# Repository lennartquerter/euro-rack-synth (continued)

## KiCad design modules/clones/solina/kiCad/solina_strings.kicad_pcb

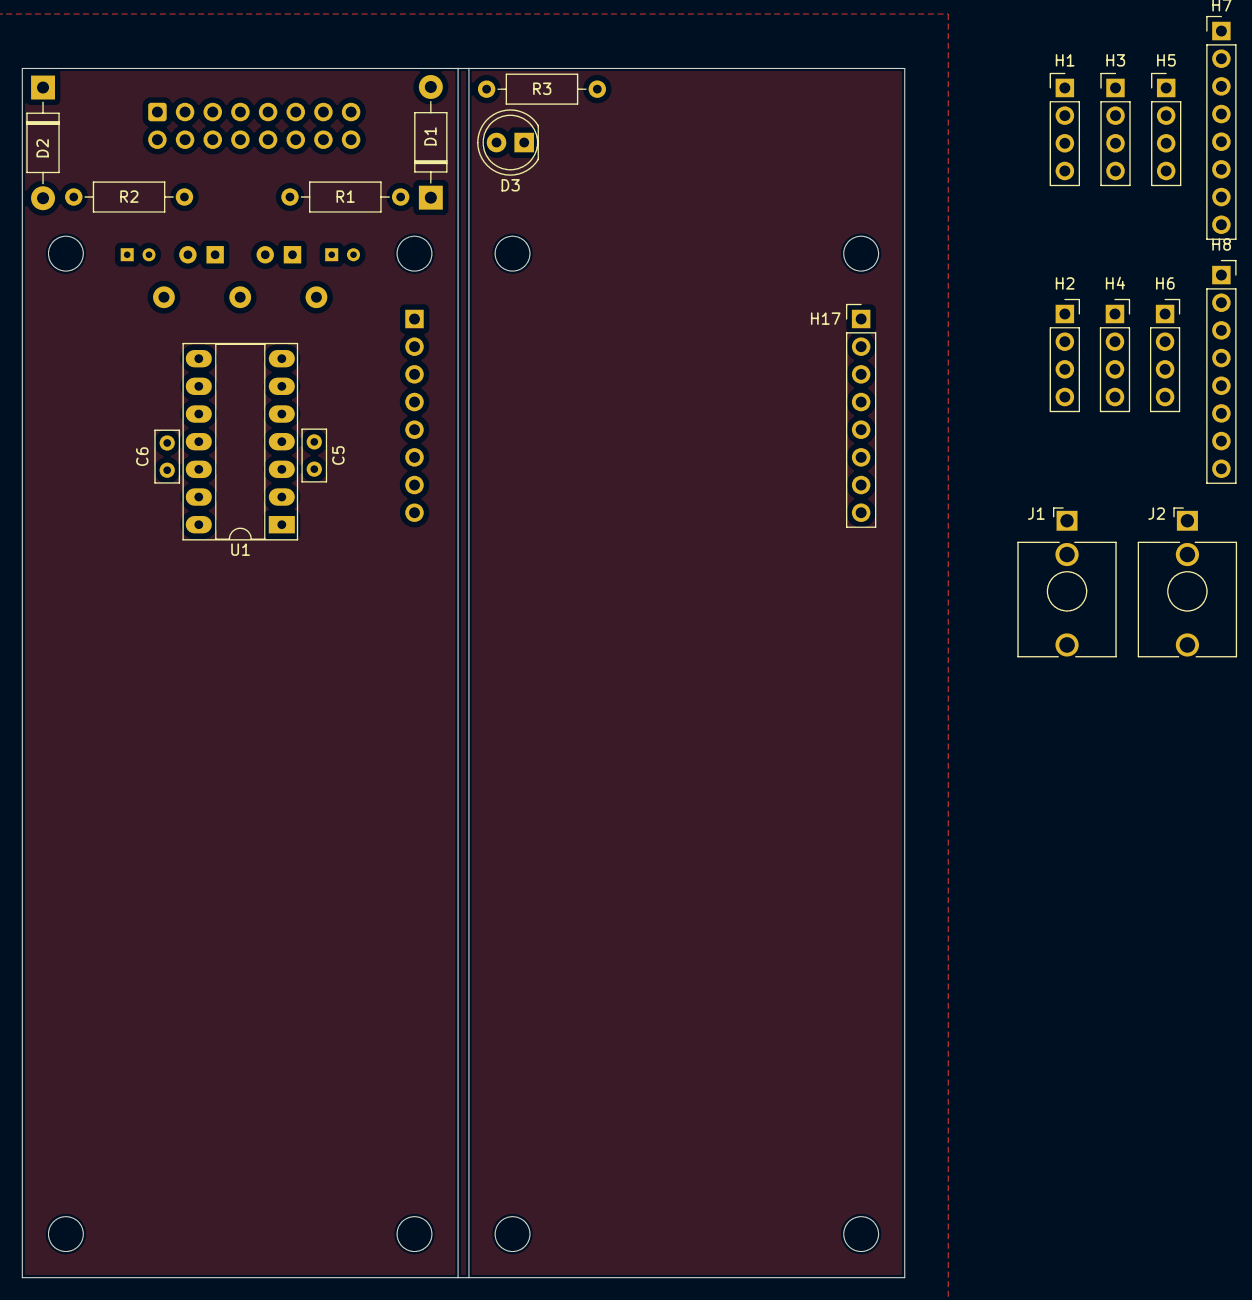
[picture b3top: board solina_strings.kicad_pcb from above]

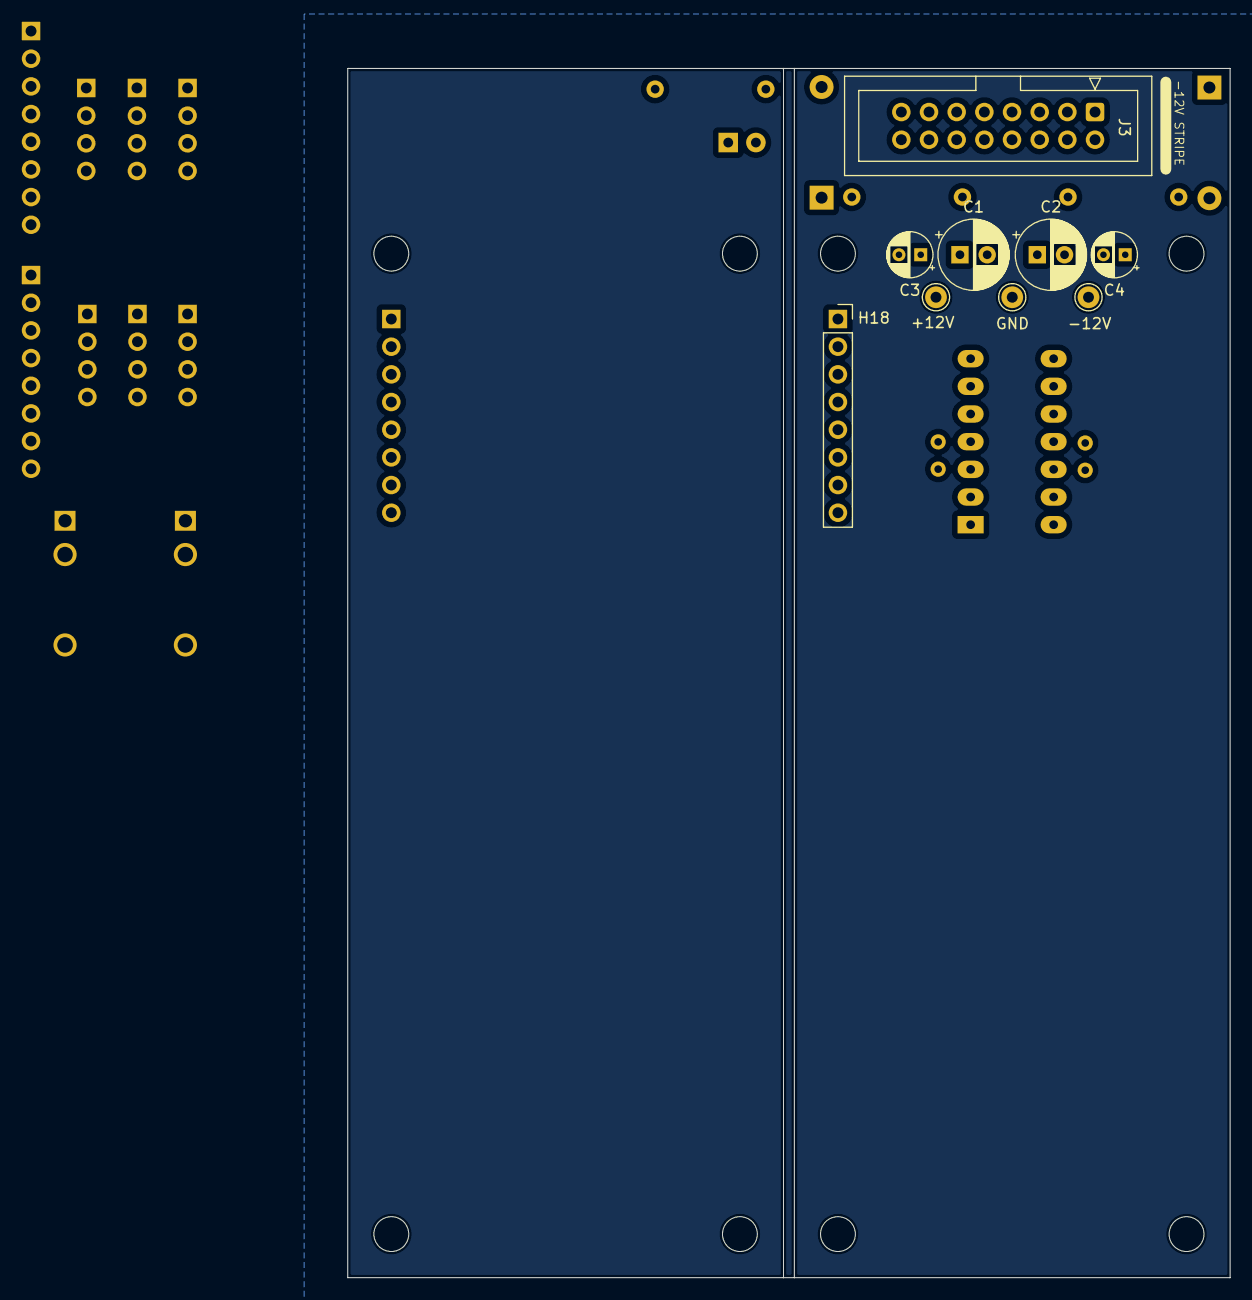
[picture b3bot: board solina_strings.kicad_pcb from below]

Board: 2 copper layers, 81.0 x 111.0 mm, 37 parts (9 on the bottom side), 12 nets, no tracks yet.

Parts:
C1, C2: 47uF; CP_Radial_D6.3mm_P2.50mm
C3, C4: 0.1uF; CP_Radial_D4.0mm_P2.00mm
C5, C6: 0.1uF; C_Rect_L4.6mm_W2.0mm_P2.50mm_MKS02_FKP02
D1, D2: 1N5819; D_DO-41_SOD81_P10.16mm_Horizontal
D3: LED; LED_D5.0mm (center Aligned)
H1: H1; PinHeader_1x04_P2.54mm_Vertical
H2: H3; PinSocket_1x04_P2.54mm_Vertical
H3: H5; PinHeader_1x04_P2.54mm_Vertical
H4: H6; PinSocket_1x04_P2.54mm_Vertical
H5: H7; PinHeader_1x04_P2.54mm_Vertical
H6: H8; PinSocket_1x04_P2.54mm_Vertical
H7: H2; PinHeader_1x08_P2.54mm_Vertical
H8: H4; PinSocket_1x08_P2.54mm_Vertical
H9, H10, H11, H12, H13, H14, H15, H16: MountingHole; MountingHole_3.2mm_M3
H17: H17; PinHeader_1x08_P2.54mm_Vertical
H18: H18; PinSocket_1x08_P2.54mm_Vertical
J1: INPUT; Jack_3.5mm_QingPu_WQP-PJ398SM_Vertical_CircularHoles
J2: OUTPUT; Jack_3.5mm_QingPu_WQP-PJ398SM_Vertical_CircularHoles
J3: PWR; IDC-Header_2x08_P2.54mm_Vertical
R1, R2: 10; R_Default (DIN0207)
R3: 500R; R_Default (DIN0207)
TP1: +12V; Pin_D1.0mm_L10.0mm
TP2: GND; Pin_D1.0mm_L10.0mm
TP3: -12V; Pin_D1.0mm_L10.0mm
U1: TL074; DIP-14_W7.62mm_Socket_LongPads

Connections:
+12V: C1.1, C3.1, C5.1, D3.2 (A), H17.1, H17.2, H18.1 (Pin_3), H18.2, R1.2, TP1.1, U1.4 (V+)
-12V: C2.2, C4.2, C6.2, H17.7, H17.8, H18.7, H18.8, R2.2, TP3.1, U1.11 (V-)
GNDREF: C1.2, C2.1, C3.2, C4.1, C5.2, C6.1, H17.3, H17.4, H17.5, H17.6, H18.3, H18.4, H18.5, H18.6, J1.S, J2.S, J3.3 (GND), J3.4 (GND), J3.5 (GND), J3.6 (GND), J3.7 (GND), J3.8 (GND), R3.1, TP2.1, U1.3 (+), U1.5 (+), U1.10 (+), U1.12 (+)
unnamed: D1.2 (A), J3.9 (+12V), J3.10 (+12V)
unnamed: D1.1 (K), R1.1
unnamed: D2.2 (A), R2.1
unnamed: D2.1 (K), J3.1 (-12V), J3.2 (-12V)
unnamed: D3.1 (K), R3.2
unnamed: U1.1, U1.2 (-)
unnamed: U1.6 (-), U1.7
unnamed: U1.8, U1.9 (-)
unnamed: U1.13 (-), U1.14

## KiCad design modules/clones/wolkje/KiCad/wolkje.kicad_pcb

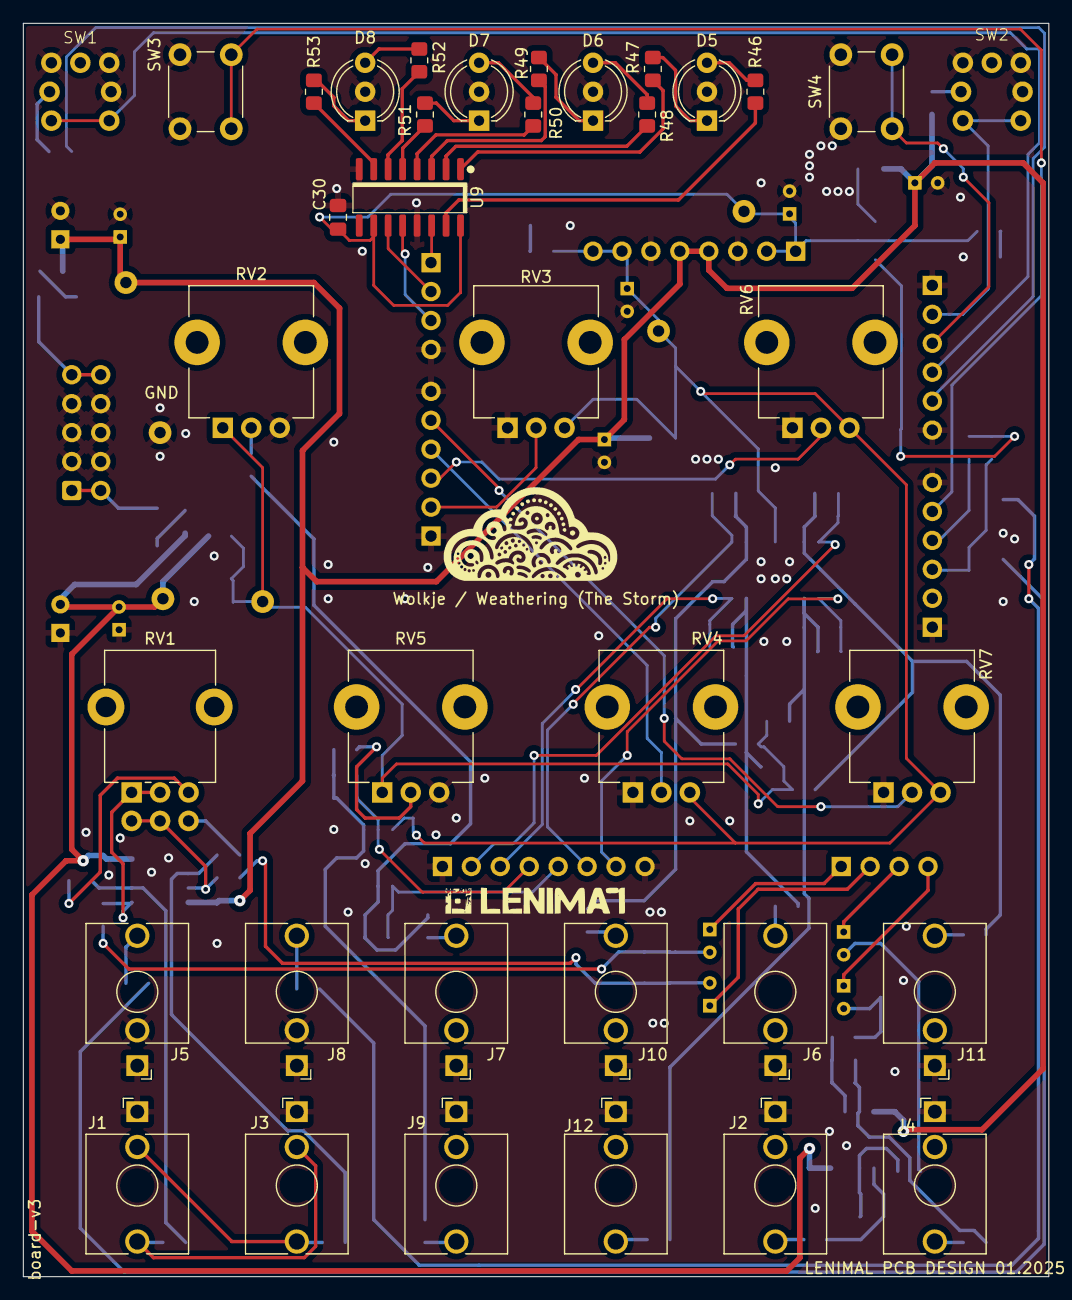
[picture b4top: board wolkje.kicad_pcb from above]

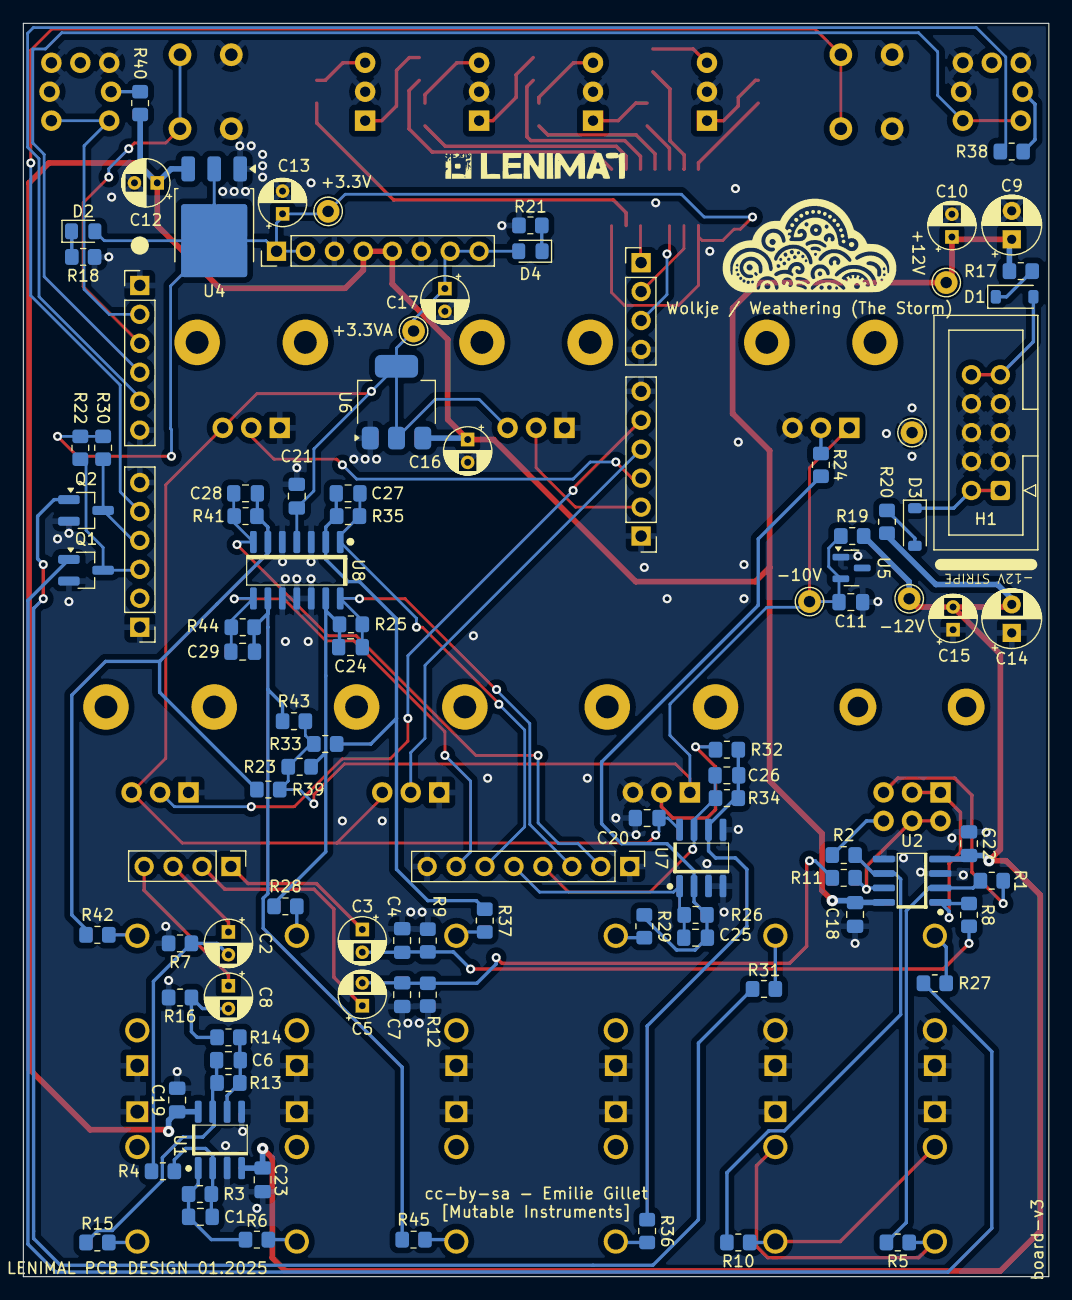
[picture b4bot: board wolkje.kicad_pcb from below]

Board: 2 copper layers, 90.0 x 110.0 mm, 132 parts (95 on the bottom side), 90 nets.

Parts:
C1, C6: 18pF; C_0805_2012Metric_Pad1.18x1.45mm_HandSolder
C2, C3, C5, C8, C12, C13, C16, C17: 10uF; CP_Radial_D4.0mm_P2.00mm
C4, C7: 220pF; C_0805_2012Metric_Pad1.18x1.45mm_HandSolder
C9, C14: 47uF; CP_Radial_D5.0mm_P2.50mm
C10, C15: 100nF; CP_Radial_D4.0mm_P2.00mm
C11, C18, C19, C20, C21, C22, C23, C30: 100nF; C_0805_2012Metric_Pad1.18x1.45mm_HandSolder
C24, C25, C26, C27, C28, C29: 1nF; C_0805_2012Metric_Pad1.18x1.45mm_HandSolder
D1, D3: 1N5819; D_SOD-123
D2, D4: LED; LED_0805_2012Metric_Pad1.15x1.40mm_HandSolder
D5: LED_4; LED_D5.0mm-3_DUAL
D6: LED_3; LED_D5.0mm-3_DUAL
D7: LED_2; LED_D5.0mm-3_DUAL
D8: LED_1; LED_D5.0mm-3_DUAL
H1: Conn_02x05_PWR_Eurorack; IDC-Header_2x05_P2.54mm_Vertical
J1: IN_L; Jack_3.5mm_QingPu_WQP-PJ398SM_Vertical_CircularHoles
J2: OUT_L; Jack_3.5mm_QingPu_WQP-PJ398SM_Vertical_CircularHoles
J3: IN_R; Jack_3.5mm_QingPu_WQP-PJ398SM_Vertical_CircularHoles
J4: OUT_R; Jack_3.5mm_QingPu_WQP-PJ398SM_Vertical_CircularHoles
J5: FREEZE_IN; Jack_3.5mm_QingPu_WQP-PJ398SM_Vertical_CircularHoles
J6: V/OCT_IN; Jack_3.5mm_QingPu_WQP-PJ398SM_Vertical_CircularHoles
J7: POSITION_IN; Jack_3.5mm_QingPu_WQP-PJ398SM_Vertical_CircularHoles
J8: TRIGGER_IN; Jack_3.5mm_QingPu_WQP-PJ398SM_Vertical_CircularHoles
J9: DENSITY_IN; Jack_3.5mm_QingPu_WQP-PJ398SM_Vertical_CircularHoles
J10: SIZE_IN; Jack_3.5mm_QingPu_WQP-PJ398SM_Vertical_CircularHoles
J11: BLEND_IN; Jack_3.5mm_QingPu_WQP-PJ398SM_Vertical_CircularHoles
J12: TEXTURE_IN; Jack_3.5mm_QingPu_WQP-PJ398SM_Vertical_CircularHoles
Q1, Q2: MMBT3904; SOT-23_Handsoldering
R1, R2: 3K3; R_0805_2012Metric_Pad1.20x1.40mm_HandSolder
R3, R7, R13, R16: 39K; R_0805_2012Metric_Pad1.20x1.40mm_HandSolder
R4, R8, R9, R11, R12, R14: 5K6; R_0805_2012Metric_Pad1.20x1.40mm_HandSolder
R5, R10: 22K; R_0805_2012Metric_Pad1.20x1.40mm_HandSolder
R6, R15: 1K; R_0805_2012Metric_Pad1.20x1.40mm_HandSolder
R17, R20: 10R; R_0805_2012Metric_Pad1.20x1.40mm_HandSolder
R18, R21, R38, R40: 2K; R_0805_2012Metric_Pad1.20x1.40mm_HandSolder
R19: 470R; R_0805_2012Metric_Pad1.20x1.40mm_HandSolder
R22, R30: 10K; R_0805_2012Metric_Pad1.20x1.40mm_HandSolder
R23: 180K; R_0805_2012Metric_Pad1.20x1.40mm_HandSolder
R24, R32, R33, R39, R43: 200K; R_0805_2012Metric_Pad1.20x1.40mm_HandSolder
R25: 47K; R_0805_2012Metric_Pad1.20x1.40mm_HandSolder
R26, R34, R44: 66.5K; R_0805_2012Metric_Pad1.20x1.40mm_HandSolder
R27, R28, R29, R31, R36, R37, R42, R45: 100K; R_0805_2012Metric_Pad1.20x1.40mm_HandSolder
R35, R41: 33K; R_0805_2012Metric_Pad1.20x1.40mm_HandSolder
R46, R47, R48, R49, R50, R51, R52, R53: 680R; R_0805_2012Metric_Pad1.20x1.40mm_HandSolder
RV1: A50K; Potentiometer_Alpha_RD902F
RV2, RV3, RV4, RV5, RV6, RV7: B10K; Potentiometer_TT_P0915N
SW1, SW2: SW_ML6; ML6-H2T2GQA
SW3: SW_RESEVERD; SW_PUSH_6mm
SW4: SW_MODE; SW_PUSH_6mm
TP1: GND; Pin_D1.0mm_L10.0mm
TP2: +3.3V; Pin_D1.0mm_L10.0mm
TP3: -10V; Pin_D1.0mm_L10.0mm
TP4: +12V; Pin_D1.0mm_L10.0mm
TP5: -12V; Pin_D1.0mm_L10.0mm
TP6: +3.3VA; Pin_D1.0mm_L10.0mm
U1, U2: TL072; SOIC-8
U3: wolkje-brain
U4: LM1117-3.3; TO-252-3_TabPin2
U5: LM4040DBZ-10; SOT-23
U6: LM1117-3.3; SOT-223-3_TabPin2
U7: MCP6002; SOIC-8
U8: MCP6004; SOIC-14
U9: 74HC595; SOIC-16

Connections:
+3.3V: C13.1, C30.2, D2.2 (A), R22.2, R30.2, TP2.1, U3.41 (+3.3V), U3.42 (+3.3V), U4.2 (VO), U9.10 (~SRCLR), U9.16 (VCC)
+3.3VA: C17.1, C20.1, C21.1, D4.2 (A), RV3.3, RV4.3, RV6.3, RV7.3, TP6.1, U3.35 (+3.3VA), U3.36 (+3.3VA), U6.2 (VO), U7.8 (V+), U8.4 (V+)
+12V: C9.1, C10.1, C12.1, C16.1, C18.1, C19.1, R17.2, R40.2, TP4.1, U1.8 (V+), U2.8 (V+), U3.38 (+12V), U3.39 (+12V), U4.3 (VI), U6.3 (VI)
-10V: C11.2, R19.2, R23.1, R33.1, R39.1, R43.1, RV2.1, RV5.1, TP3.1, U5.2 (A)
-12V: C14.2, C15.2, C22.2, C23.2, R19.1, R20.2, TP5.1, U1.4 (V-), U2.4 (V-)
/inputs/BLEND: RV7.2, U3.29 (Blend)
/inputs/BLEND_CV: C28.1, R41.2, U3.23 (CV_Blend), U8.7
/inputs/DENSITY: C26.1, R34.2, U3.21 (CV_Density), U7.7
/inputs/FREEZE_LED: R38.2, U3.5 (LED_FREEZE)
/inputs/FREEZE_TRIGGER: Q1.3 (C), R22.1, U3.10 (TRIG_Freeze)
/inputs/PITCH: RV6.2, U3.27 (Pitch)
/inputs/PLAY_TRIGGER: Q2.3 (C), R30.1, U3.9 (TRIG_Play)
/inputs/POSITION: C25.1, R26.2, U3.20 (CV_Position), U7.1
/inputs/SIZE: RV3.2, U3.26 (Size)
/inputs/SIZE_CV: C27.1, R35.2, U3.19 (CV_Size), U8.1
/inputs/SW_FREEZE: SW1.1, SW1.2, U3.4 (SW_Freeze)
/inputs/SW_LOAD: SW2.1, SW2.2, U3.2 (SW_Load)
/inputs/SW_MODE: SW4.2, U3.3 (SW_Mode)
/inputs/SW_RESERVED: SW3.2, U3.8 (NC_2)
/inputs/TEXTURE: RV4.2, U3.28 (Texture)
/inputs/TEXTURE_CV: C29.1, R44.2, U3.18 (CV_Texture), U8.8
/inputs/V/OCT: C24.1, R25.2, U3.22 (CV_V/OCT), U8.14
/led_driver/CLK: U3.33 (LED_CLK), U9.11 (SRCLK)
/led_driver/ENABLE: U3.32 (LED_CS), U9.12 (RCLK)
/led_driver/SER: U3.34 (LED_DATA), U9.14 (SER)
GNDREF: C4.1, C7.1, C9.2, C10.2, C11.1, C12.2, C13.2, C14.1, C15.1, C16.2, C17.2, C18.2, C19.2, C20.2, C21.2, C22.1, C23.1, C30.1, D5.3 (K), D6.3 (K), D7.3 (K), D8.3 (K), H1.3, H1.4, H1.5, H1.6, H1.7, H1.8, J1.S, J2.S, J3.S, J4.S, J5.S, J5.TN, J6.S, J7.S, J8.S, J8.TN, J9.S, J10.S, J11.S, J12.S, Q1.2 (E), Q2.2 (E), R7.2, R9.1, R12.1, R16.2, R18.1, R21.1, RV2.3, RV3.1, RV4.1, RV5.3, RV6.1, RV7.1, SW1.3, SW1.4 (A), SW1.L2, SW2.3, SW2.4 (A), SW2.L2, SW3.1, SW4.1, TP1.1, U1.3 (+), U1.5 (+), U2.3 (+), U2.5 (+), U3.1 (VSS), U3.6 (VSS), U3.7 (VSS), U3.12 (VSS), U3.17 (VSS), U3.24 (VSS), U3.25 (VSS), U3.30 (VSS), U3.31 (VSS), U3.37 (VSS), U3.40 (VSS), U4.1 (GND), U5.1 (K), U6.1 (GND), U7.3 (+), U7.4 (V-), U7.5 (+), U8.3 (+), U8.5 (+), U8.10 (+), U8.11 (V-), U8.12 (+), U9.8 (GND), U9.13 (~OE)
unnamed: C1.1, R3.2, R6.1, U1.1
unnamed: C2.2, R4.2, R7.1
unnamed: C3.2, C4.2, R8.2, R9.2
unnamed: C5.2, C7.2, R11.2, R12.2
unnamed: C6.1, R13.2, R15.1, U1.7
unnamed: C8.2, R14.2, R16.1
unnamed: D1.2 (A), H1.9, H1.10
unnamed: D1.1 (K), R17.1
unnamed: D2.1 (K), R18.2
unnamed: D3.2 (A), R20.1
unnamed: D3.1 (K), H1.1, H1.2
unnamed: D4.1 (K), R21.2
unnamed: D5.1 (A1), R47.2
unnamed: D5.2 (A2), R46.2
unnamed: D6.1 (A1), R49.2
unnamed: D6.2 (A2), R48.2
unnamed: D7.1 (A1), R51.2
unnamed: D7.2 (A2), R50.2
unnamed: D8.1 (A1), R53.2
unnamed: D8.2 (A2), R52.2
unnamed: J1.T, J3.TN, R5.1
unnamed: J1.TN, J3.T, R10.1
unnamed: J2.T, R6.2
unnamed: J4.T, R15.2
unnamed: J5.T, R27.2
unnamed: J6.T, R28.1
unnamed: J7.T, R29.1
unnamed: J8.T, R31.2
unnamed: J9.T, R36.1
unnamed: J10.T, R37.1
unnamed: J11.T, R42.1
unnamed: J12.T, R45.1
unnamed: Q1.1 (B), R27.1
unnamed: Q2.1 (B), R31.1
unnamed: R1.2, RV1.3
unnamed: R2.2, RV1.6
unnamed: R8.1, RV1.1, RV1.2, U2.1
unnamed: R11.1, RV1.4, RV1.5, U2.7
unnamed: R24.1, RV2.2
unnamed: R32.1, RV5.2
unnamed: R38.1, SW1.L1
unnamed: R40.1, SW2.L1
unnamed: C1.2, R3.1, R4.1, U1.2 (-)
unnamed: C6.2, R13.1, R14.1, U1.6 (-)
unnamed: R1.1, R5.2, U2.2 (-)
unnamed: R2.1, R10.2, U2.6 (-)
unnamed: C3.1, U3.16 (IN_L)
unnamed: C5.1, U3.15 (IN_R)
unnamed: C2.1, U3.14 (OUT_L)
unnamed: C8.1, U3.13 (OUT_R)
unnamed: C25.2, R24.2, R26.1, R29.2, U7.2 (-)
unnamed: C26.2, R32.2, R34.1, R36.2, U7.6 (-)
unnamed: C27.2, R33.2, R35.1, R37.2, U8.2 (-)
unnamed: C28.2, R39.2, R41.1, R42.2, U8.6 (-)
unnamed: C29.2, R43.2, R44.1, R45.2, U8.9 (-)
unnamed: C24.2, R23.2, R25.1, R28.2, U8.13 (-)
unnamed: R46.1, U9.15 (QA)
unnamed: R47.1, U9.1 (QB)
unnamed: R48.1, U9.2 (QC)
unnamed: R49.1, U9.3 (QD)
unnamed: R50.1, U9.4 (QE)
unnamed: R51.1, U9.5 (QF)
unnamed: R52.1, U9.6 (QG)
unnamed: R53.1, U9.7 (QH)

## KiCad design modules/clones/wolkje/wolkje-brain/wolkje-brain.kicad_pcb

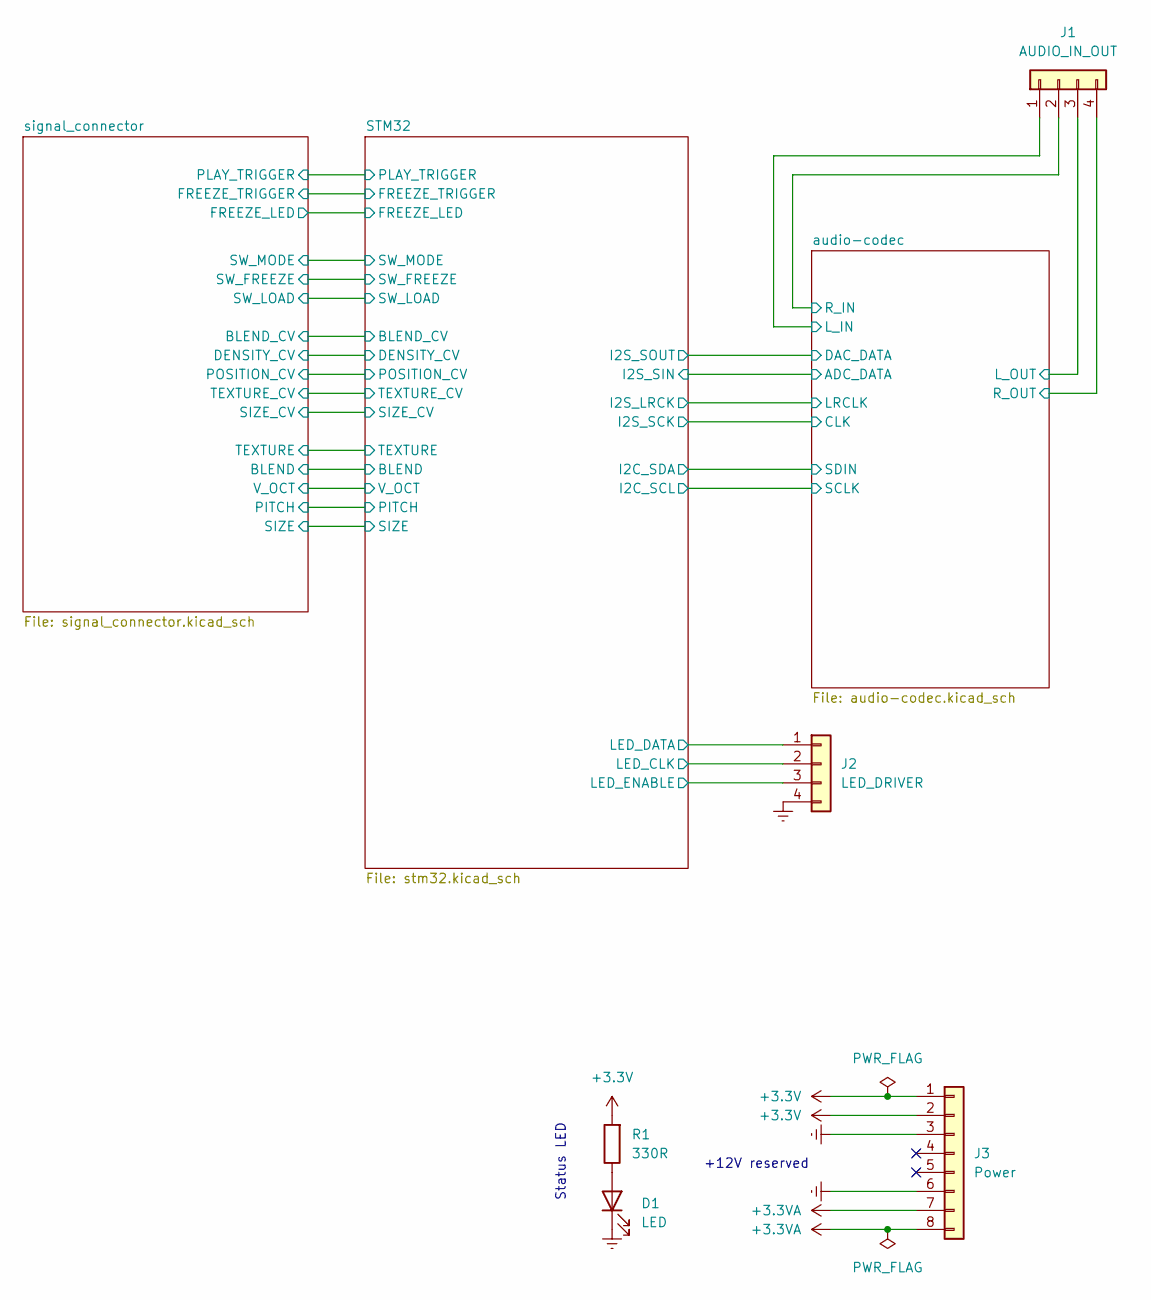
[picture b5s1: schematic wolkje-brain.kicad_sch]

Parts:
D1: LED; LED_0805_2012Metric_Pad1.15x1.40mm_HandSolder
J1: AUDIO_IN_OUT; PinHeader_1x04_P2.54mm_Vertical
J2: LED_DRIVER; PinHeader_1x04_P2.54mm_Vertical
J3: Power; PinHeader_1x08_P2.54mm_Vertical
R1: 330R; R_0805_2012Metric_Pad1.20x1.40mm_HandSolder

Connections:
+3.3V: J3.1, J3.2, R1.2; also elsewhere on the board
+3.3VA: J3.7, J3.8; also elsewhere on the board
/STM32/LED_CLK: J2.2; also elsewhere on the board
/STM32/LED_DATA: J2.1; also elsewhere on the board
/STM32/LED_ENABLE: J2.3; also elsewhere on the board
/audio-codec/L_IN: J1.1; also elsewhere on the board
/audio-codec/L_OUT: J1.3; also elsewhere on the board
/audio-codec/R_IN: J1.2; also elsewhere on the board
/audio-codec/R_OUT: J1.4; also elsewhere on the board
GNDREF: D1.1 (K), J2.4, J3.3, J3.6; also elsewhere on the board
unnamed: D1.2 (A), R1.1

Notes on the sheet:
Status LED
+12V reserved

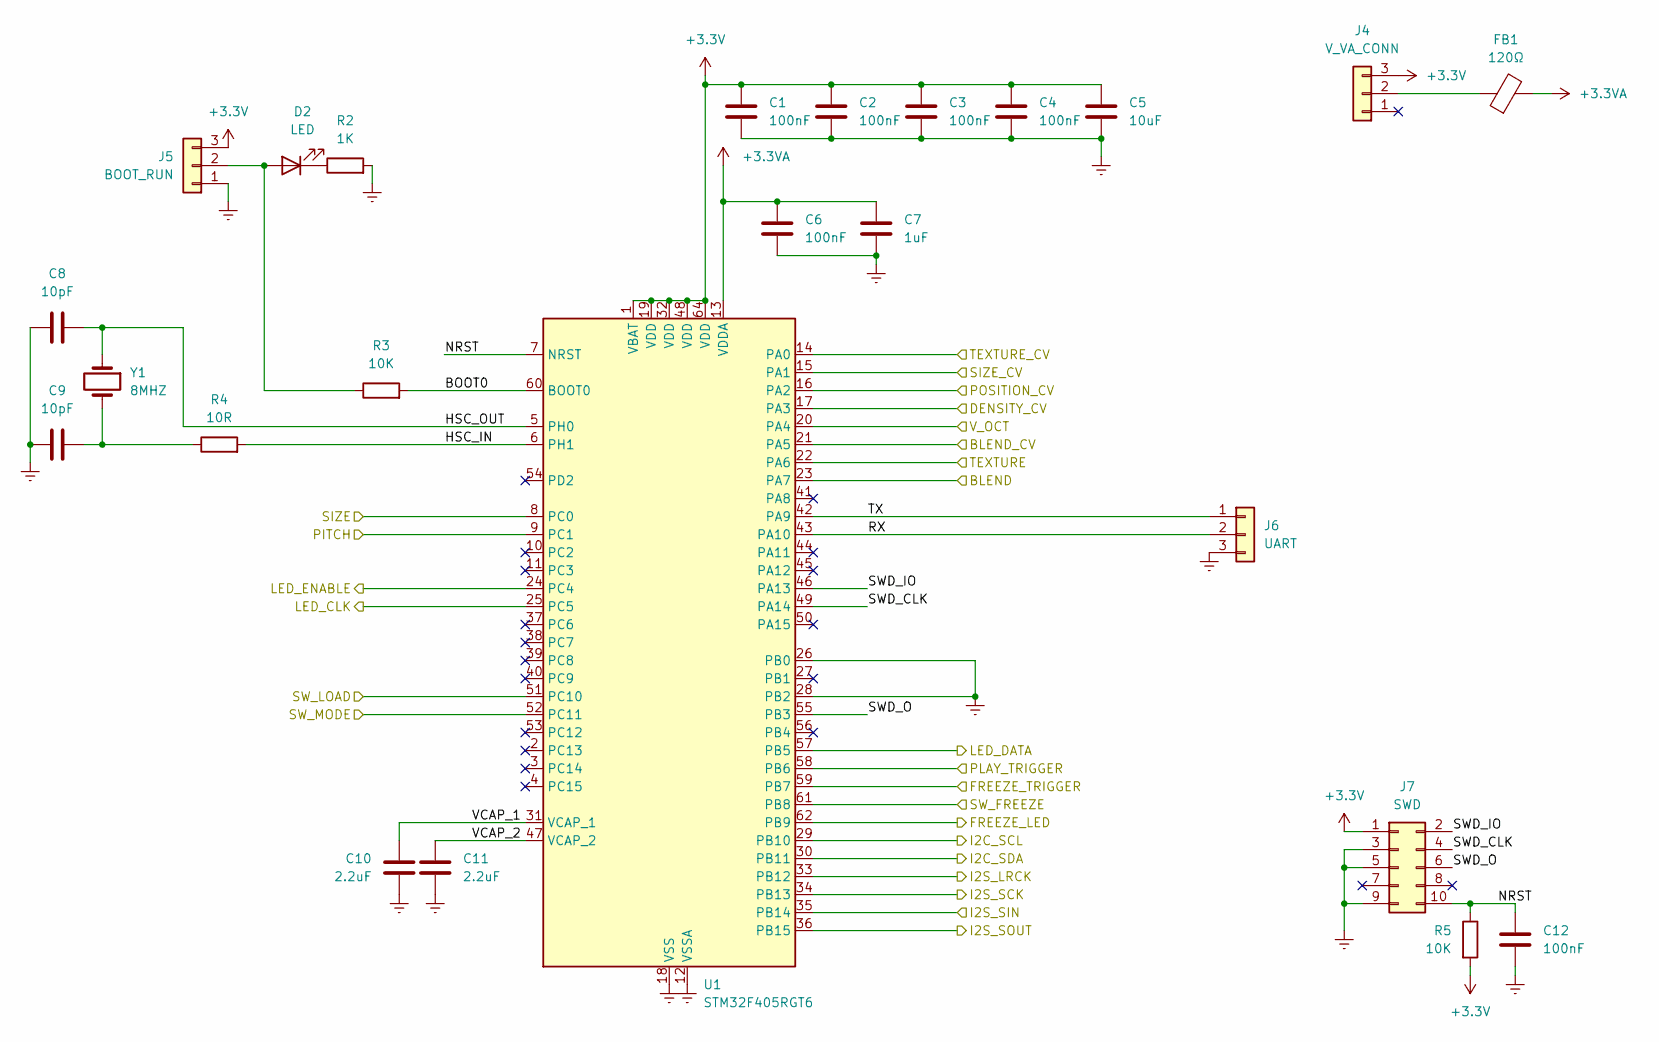
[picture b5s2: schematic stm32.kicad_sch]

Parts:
C1, C2, C3, C4, C6, C12: 100nF; C_0805_2012Metric_Pad1.18x1.45mm_HandSolder
C5: 10uF; C_0805_2012Metric_Pad1.18x1.45mm_HandSolder
C7: 1uF; C_0805_2012Metric_Pad1.18x1.45mm_HandSolder
C8, C9: 10pF; C_0805_2012Metric_Pad1.18x1.45mm_HandSolder
C10, C11: 2.2uF; C_0805_2012Metric_Pad1.18x1.45mm_HandSolder
D2: LED; LED_0805_2012Metric_Pad1.15x1.40mm_HandSolder
FB1: 120Ω; L_0805_2012Metric_Pad1.15x1.40mm_HandSolder
J4: V_VA_CONN; PinHeader_1x03_P2.54mm_Vertical
J5: BOOT_RUN; PinHeader_1x03_P2.54mm_Vertical
J6: UART; PinHeader_1x03_P2.54mm_Vertical
J7: SWD; PinHeader_2x05_P2.54mm_Vertical
R2: 1K; R_0805_2012Metric_Pad1.20x1.40mm_HandSolder
R3, R5: 10K; R_0805_2012Metric_Pad1.20x1.40mm_HandSolder
R4: 10R; R_0805_2012Metric_Pad1.20x1.40mm_HandSolder
U1: STM32F405RGT6; LQFP-64_10x10mm_P0.5mm
Y1: 8MHZ; Crystal_HC49-U_Vertical

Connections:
+3.3V: C1.2, C2.2, C3.2, C4.2, C5.2, J4.3, J5.3, J7.1, R5.2, U1.1 (VBAT), U1.19 (VDD), U1.32 (VDD), U1.48 (VDD), U1.64 (VDD); also elsewhere on the board
+3.3VA: C6.2, C7.2, FB1.2, U1.13 (VDDA); also elsewhere on the board
/STM32/BLEND: U1.23 (PA7); also elsewhere on the board
/STM32/BLEND_CV: U1.21 (PA5); also elsewhere on the board
/STM32/BOOT0: R3.2, U1.60 (BOOT0)
/STM32/DENSITY_CV: U1.17 (PA3); also elsewhere on the board
/STM32/FREEZE_LED: U1.62 (PB9); also elsewhere on the board
/STM32/FREEZE_TRIGGER: U1.59 (PB7); also elsewhere on the board
/STM32/HSC_IN: R4.2, U1.6 (PH1)
/STM32/HSC_OUT: C8.1, U1.5 (PH0), Y1.1
/STM32/I2C_SCL: U1.29 (PB10); also elsewhere on the board
/STM32/I2C_SDA: U1.30 (PB11); also elsewhere on the board
/STM32/I2S_LRCK: U1.33 (PB12); also elsewhere on the board
/STM32/I2S_SCK: U1.34 (PB13); also elsewhere on the board
/STM32/I2S_SIN: U1.35 (PB14); also elsewhere on the board
/STM32/I2S_SOUT: U1.36 (PB15); also elsewhere on the board
/STM32/LED_CLK: U1.25 (PC5); also elsewhere on the board
/STM32/LED_DATA: U1.57 (PB5); also elsewhere on the board
/STM32/LED_ENABLE: U1.24 (PC4); also elsewhere on the board
/STM32/NRST: C12.2, J7.10, R5.1, U1.7 (NRST)
/STM32/PITCH: U1.9 (PC1); also elsewhere on the board
/STM32/PLAY_TRIGGER: U1.58 (PB6); also elsewhere on the board
/STM32/POSITION_CV: U1.16 (PA2); also elsewhere on the board
/STM32/RX: J6.2, U1.43 (PA10)
/STM32/SIZE: U1.8 (PC0); also elsewhere on the board
/STM32/SIZE_CV: U1.15 (PA1); also elsewhere on the board
/STM32/SWD_CLK: J7.4, U1.49 (PA14)
/STM32/SWD_IO: J7.2, U1.46 (PA13)
/STM32/SWD_O: J7.6, U1.55 (PB3)
/STM32/SW_FREEZE: U1.61 (PB8); also elsewhere on the board
/STM32/SW_LOAD: U1.51 (PC10); also elsewhere on the board
/STM32/SW_MODE: U1.52 (PC11); also elsewhere on the board
/STM32/TEXTURE: U1.22 (PA6); also elsewhere on the board
/STM32/TEXTURE_CV: U1.14 (PA0); also elsewhere on the board
/STM32/TX: J6.1, U1.42 (PA9)
/STM32/VCAP_1: C10.1, U1.31 (VCAP_1)
/STM32/VCAP_2: C11.1, U1.47 (VCAP_2)
/STM32/V_OCT: U1.20 (PA4); also elsewhere on the board
GNDREF: C1.1, C2.1, C3.1, C4.1, C5.1, C6.1, C7.1, C8.2, C9.2, C10.2, C11.2, C12.1, J5.1, J6.3, J7.3, J7.5, J7.9, R2.2, U1.12 (VSSA), U1.18 (VSS), U1.26 (PB0), U1.28 (PB2), U1.63 (VSS); also elsewhere on the board
unnamed: C9.1, R4.1, Y1.2
unnamed: D2.2 (A), J5.2, R3.1
unnamed: D2.1 (K), R2.1
unnamed: FB1.1, J4.2

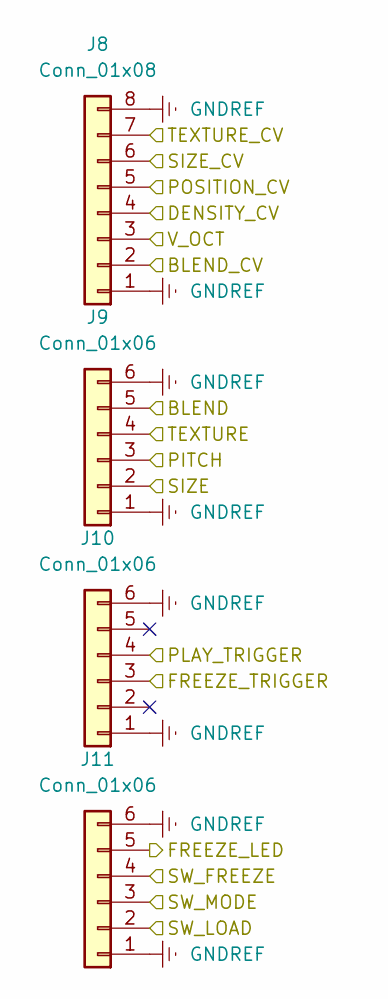
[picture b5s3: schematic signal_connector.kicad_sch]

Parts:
J8: Conn_01x08; PinHeader_1x08_P2.54mm_Vertical
J9, J10, J11: Conn_01x06; PinHeader_1x06_P2.54mm_Vertical

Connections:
/STM32/BLEND: J9.5; also elsewhere on the board
/STM32/BLEND_CV: J8.2; also elsewhere on the board
/STM32/DENSITY_CV: J8.4; also elsewhere on the board
/STM32/FREEZE_LED: J11.5; also elsewhere on the board
/STM32/FREEZE_TRIGGER: J10.3; also elsewhere on the board
/STM32/PITCH: J9.3; also elsewhere on the board
/STM32/PLAY_TRIGGER: J10.4; also elsewhere on the board
/STM32/POSITION_CV: J8.5; also elsewhere on the board
/STM32/SIZE: J9.2; also elsewhere on the board
/STM32/SIZE_CV: J8.6; also elsewhere on the board
/STM32/SW_FREEZE: J11.4; also elsewhere on the board
/STM32/SW_LOAD: J11.2; also elsewhere on the board
/STM32/SW_MODE: J11.3; also elsewhere on the board
/STM32/TEXTURE: J9.4; also elsewhere on the board
/STM32/TEXTURE_CV: J8.7; also elsewhere on the board
/STM32/V_OCT: J8.3; also elsewhere on the board
GNDREF: J8.1, J8.8, J9.1, J9.6, J10.1, J10.6, J11.1, J11.6; also elsewhere on the board

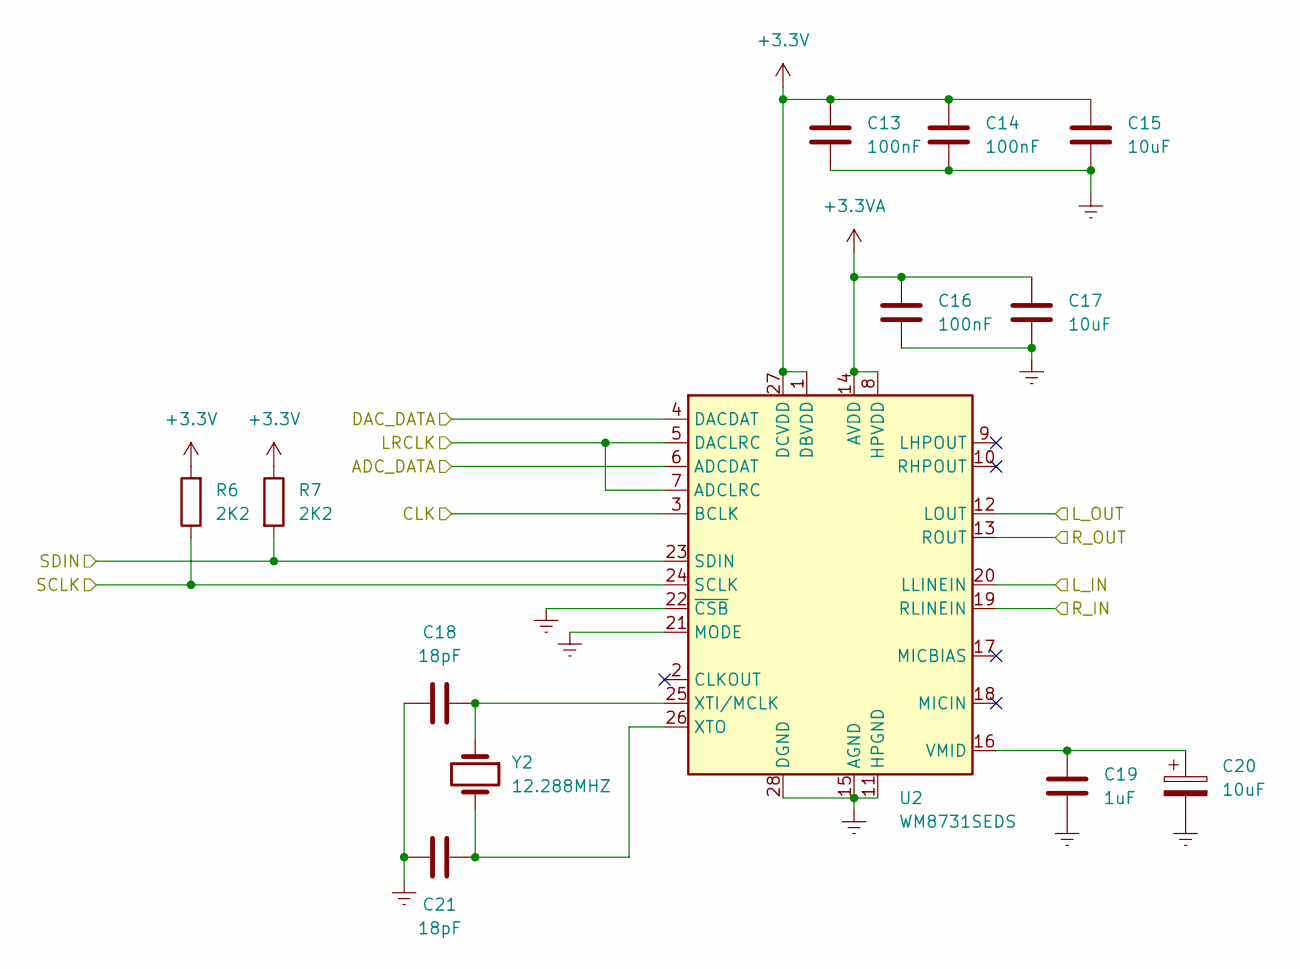
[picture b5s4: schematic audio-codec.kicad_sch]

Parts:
C13, C14, C16: 100nF; C_0805_2012Metric_Pad1.18x1.45mm_HandSolder
C15, C17: 10uF; C_0805_2012Metric_Pad1.18x1.45mm_HandSolder
C18, C21: 18pF; C_0805_2012Metric_Pad1.18x1.45mm_HandSolder
C19: 1uF; C_0805_2012Metric_Pad1.18x1.45mm_HandSolder
C20: 10uF; CP_Radial_D4.0mm_P2.00mm
R6, R7: 2K2; R_0805_2012Metric_Pad1.20x1.40mm_HandSolder
U2: WM8731SEDS; SSOP-28_5.3x10.2mm_P0.65mm
Y2: 12.288MHZ; Crystal_HC49-U_Vertical

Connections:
+3.3V: C13.2, C14.2, C15.2, R6.2, R7.1, U2.1 (DBVDD), U2.27 (DCVDD); also elsewhere on the board
+3.3VA: C16.2, C17.2, U2.8 (HPVDD), U2.14 (AVDD); also elsewhere on the board
/STM32/I2C_SCL: R6.1, U2.24 (SCLK); also elsewhere on the board
/STM32/I2C_SDA: R7.2, U2.23 (SDIN); also elsewhere on the board
/STM32/I2S_LRCK: U2.5 (DACLRC), U2.7 (ADCLRC); also elsewhere on the board
/STM32/I2S_SCK: U2.3 (BCLK); also elsewhere on the board
/STM32/I2S_SIN: U2.6 (ADCDAT); also elsewhere on the board
/STM32/I2S_SOUT: U2.4 (DACDAT); also elsewhere on the board
/audio-codec/L_IN: U2.20 (LLINEIN); also elsewhere on the board
/audio-codec/L_OUT: U2.12 (LOUT); also elsewhere on the board
/audio-codec/R_IN: U2.19 (RLINEIN); also elsewhere on the board
/audio-codec/R_OUT: U2.13 (ROUT); also elsewhere on the board
GNDREF: C13.1, C14.1, C15.1, C16.1, C17.1, C18.2, C19.1, C20.2, C21.2, U2.11 (HPGND), U2.15 (AGND), U2.21 (MODE), U2.22 (~CSB), U2.28 (DGND); also elsewhere on the board
unnamed: C19.2, C20.1, U2.16 (VMID)
unnamed: C18.1, U2.25 (XTI/MCLK), Y2.1
unnamed: C21.1, U2.26 (XTO), Y2.2
